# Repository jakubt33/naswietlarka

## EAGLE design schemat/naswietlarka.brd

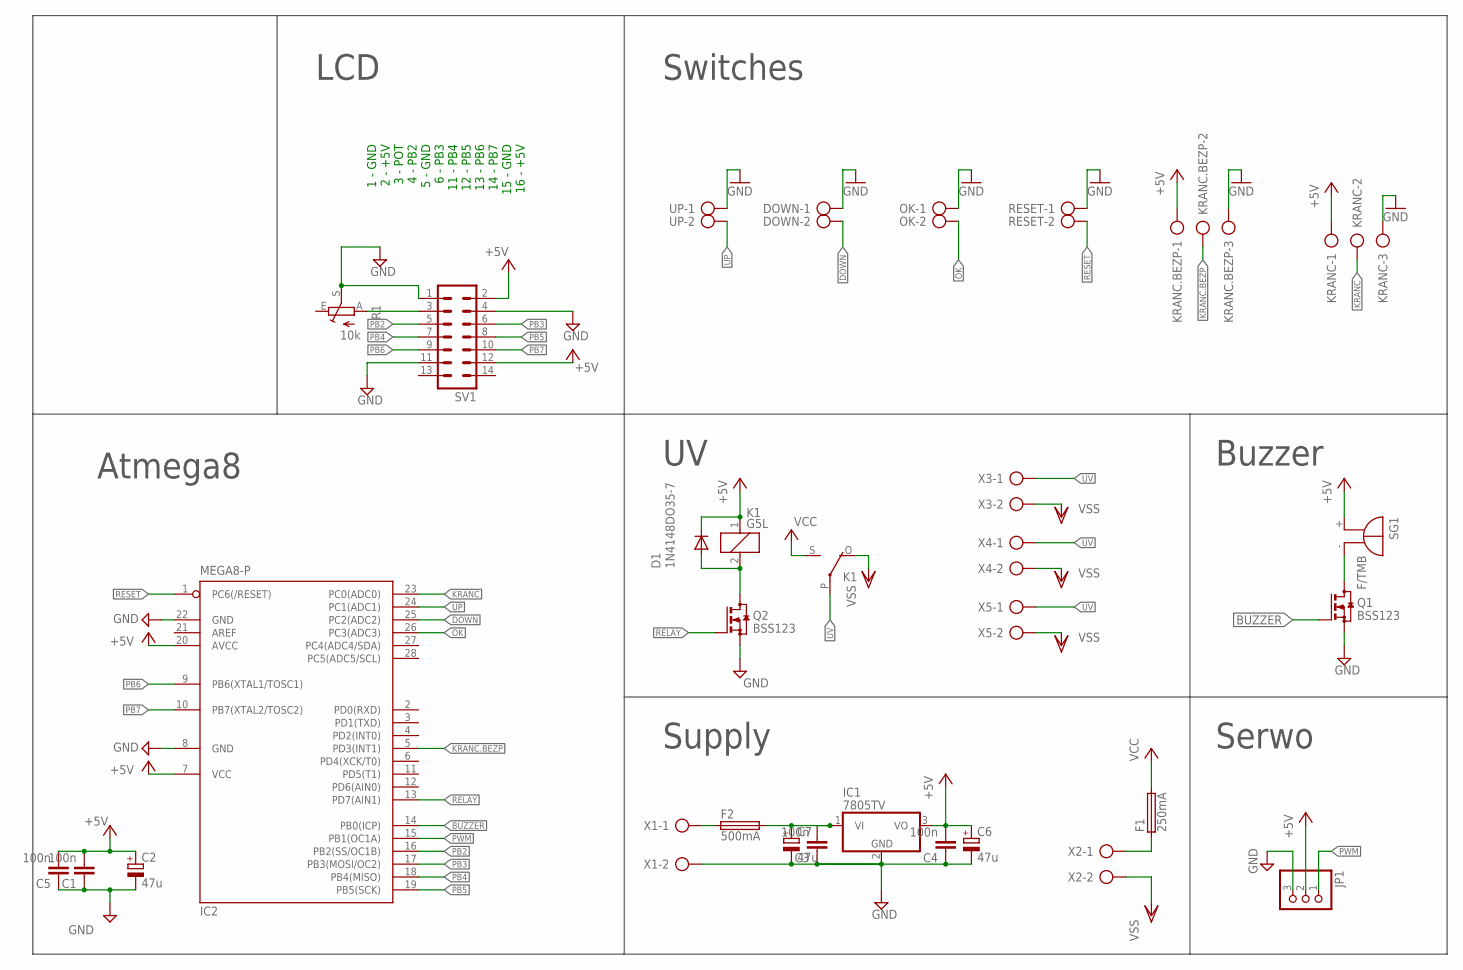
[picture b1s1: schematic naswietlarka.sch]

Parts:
C1, C3, C4, C5: 100n; C0805
C2, C6, C7: 47u; E2,5-5
D1: 1N4148DO35-7; DO35-7
DOWN: AK300/2
F1: 250mA; SH22,5
F2: 500mA; SH22,5
IC1: 7805TV; TO220V
IC2: MEGA8-P; DIL28-3
JP1: PINHD-1X3; 1X03
K1: G5L; G5LE
KRANC, KRANC.BEZP: AK300/3
OK: AK300/2
Q1, Q2: BSS123; SOT23
R1: 10k; CA6V
RESET: AK300/2
SG1: F/TMB
SV1: ML14
UP: AK300/2
X1, X2, X3, X4, X5: AK500/2-H

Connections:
+5V: C1.2, C2.+, C4.2, C5.2, C6.+, D1.C, IC1.3 (VO), IC2.7 (VCC), IC2.20 (AVCC), JP1.2, K1.1, KRANC.1, KRANC.BEZP.1, SG1.+, SV1.2, SV1.12
BUZZER: IC2.14 (PB0(ICP)), Q1.1 (G)
DOWN: DOWN.2, IC2.25 (PC2(ADC2))
GND: C1.1, C2.-, C3.1, C4.1, C5.1, C6.-, C7.-, DOWN.1, IC1.2 (GND), IC2.8 (GND), IC2.22 (GND), JP1.3, KRANC.3, KRANC.BEZP.3, OK.1, Q1.2 (S), Q2.2 (S), R1.S, RESET.1, SV1.1, SV1.4, SV1.11, UP.1, X1.2
KRANC: IC2.23 (PC0(ADC0)), KRANC.2
KRANC.BEZP: IC2.5 (PD3(INT1)), KRANC.BEZP.2
unnamed: R1.A, SV1.3
unnamed: D1.A, K1.2, Q2.3 (D)
unnamed: F1.1, X2.1
unnamed: Q1.3 (D), SG1.-
unnamed: F2.1, X1.1
unnamed: C3.2, C7.+, F2.2, IC1.1 (VI)
OK: IC2.26 (PC3(ADC3)), OK.2
PB2: IC2.16 (PB2(SS/OC1B)), SV1.5
PB3: IC2.17 (PB3(MOSI/OC2)), SV1.6
PB4: IC2.18 (PB4(MISO)), SV1.7
PB5: IC2.19 (PB5(SCK)), SV1.8
PB6: IC2.9 (PB6(XTAL1/TOSC1)), SV1.9
PB7: IC2.10 (PB7(XTAL2/TOSC2)), SV1.10
PWM: IC2.15 (PB1(OC1A)), JP1.1
RELAY: IC2.13 (PD7(AIN1)), Q2.1 (G)
RESET: IC2.1 (PC6(/RESET)), RESET.2
UP: IC2.24 (PC1(ADC1)), UP.2
UV: K1.P, X3.1, X4.1, X5.1
VCC: F1.2, K1.S
VSS: K1.O, X2.2, X3.2, X4.2, X5.2

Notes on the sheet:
LCD
Switches
Atmega8
Supply
Buzzer
Serwo
1 - GND 2 - +5V 3 - POT 4 - PB2 5 - GND 6 - PB3 11 - PB4 12 - PB5 13 - PB6 14 - PB7 15 - GND 16 - +5V

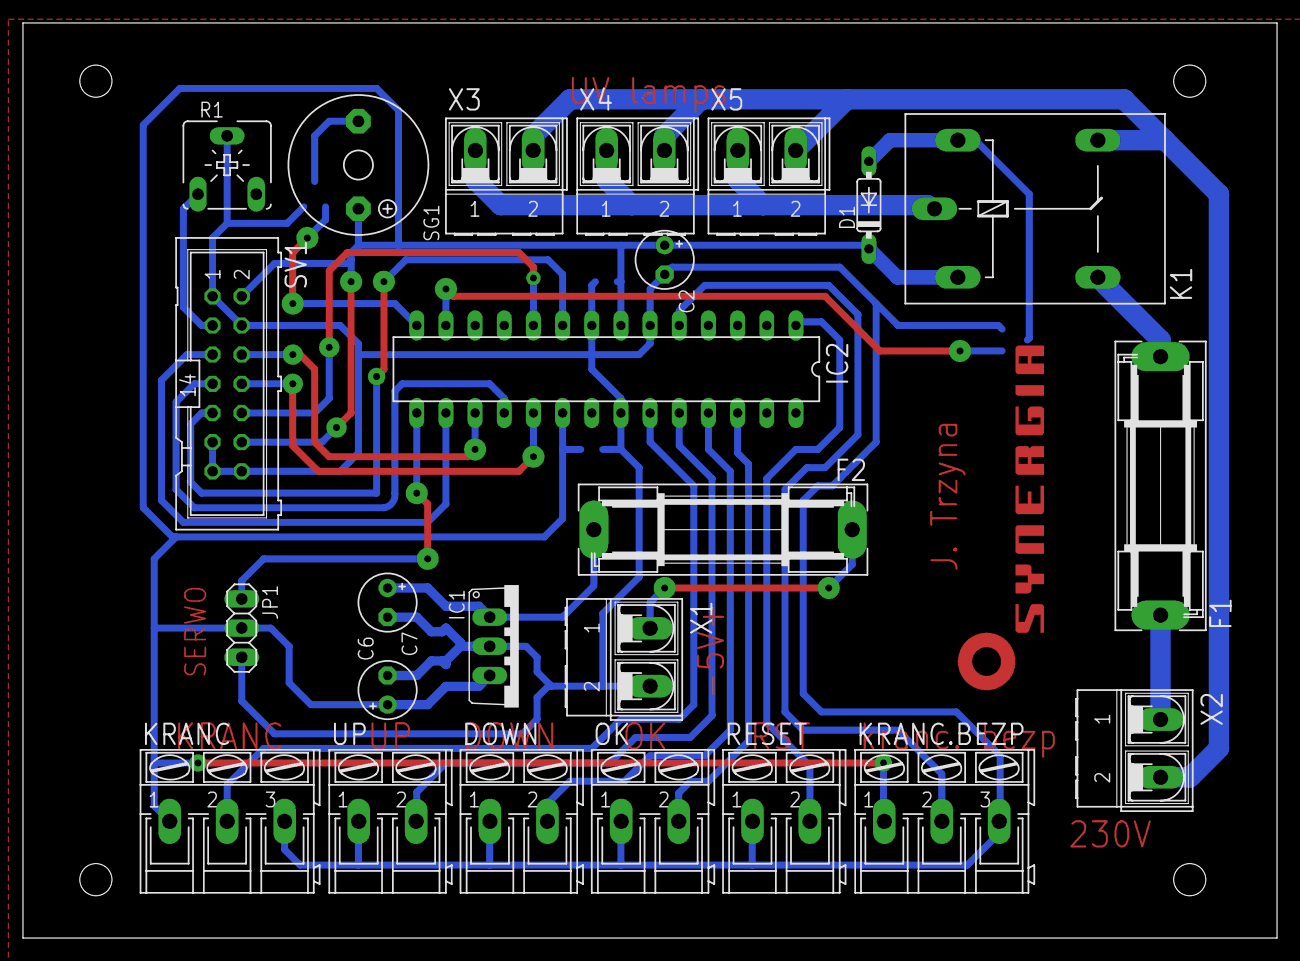
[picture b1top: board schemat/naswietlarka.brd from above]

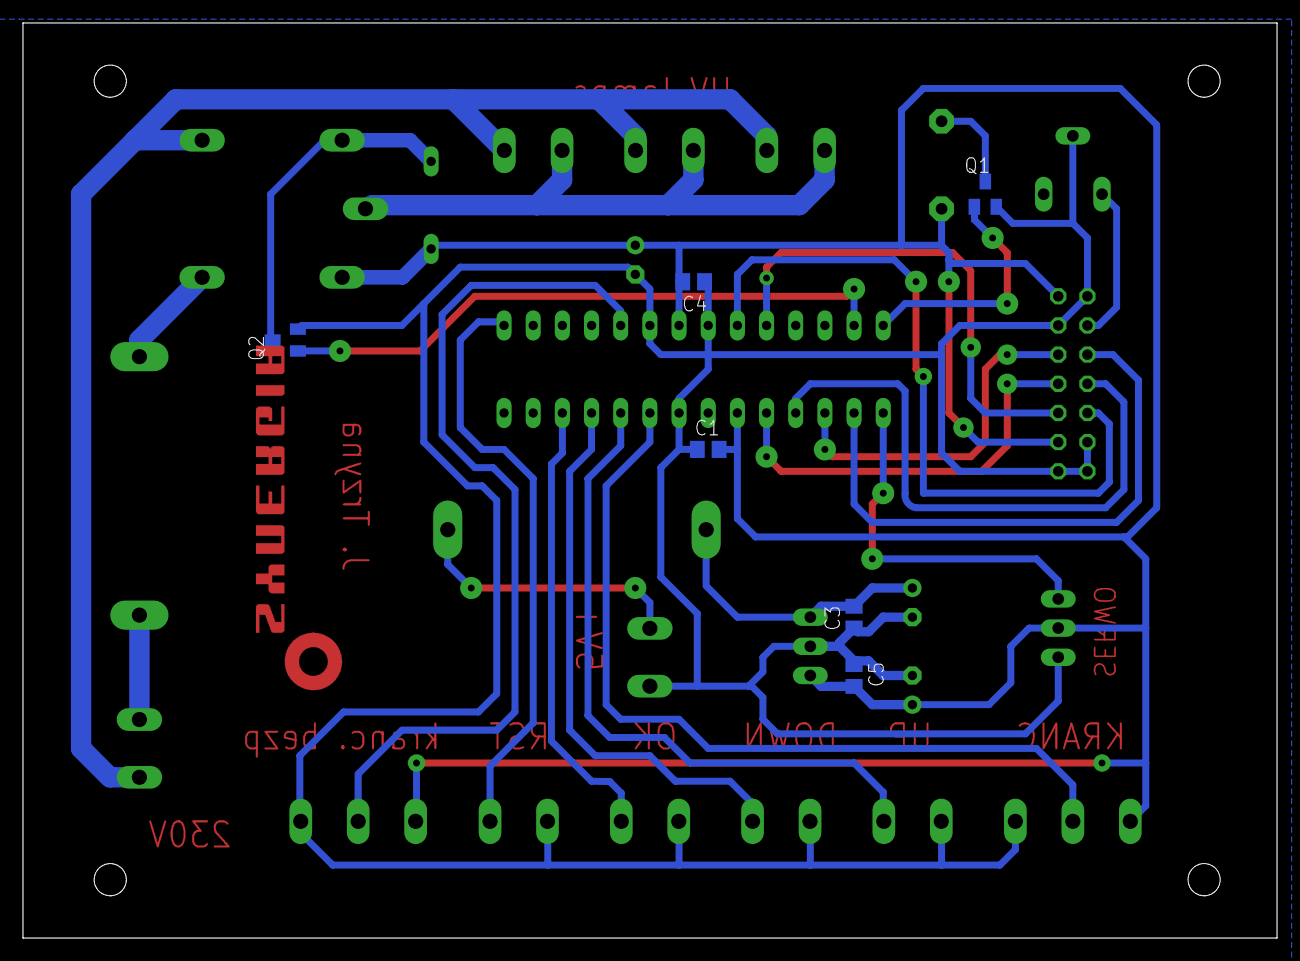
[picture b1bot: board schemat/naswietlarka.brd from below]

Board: 2 copper layers, 109.2 x 79.7 mm, 31 parts (6 on the bottom side), 26 nets.

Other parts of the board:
U$1: SYNERGIA_30MM

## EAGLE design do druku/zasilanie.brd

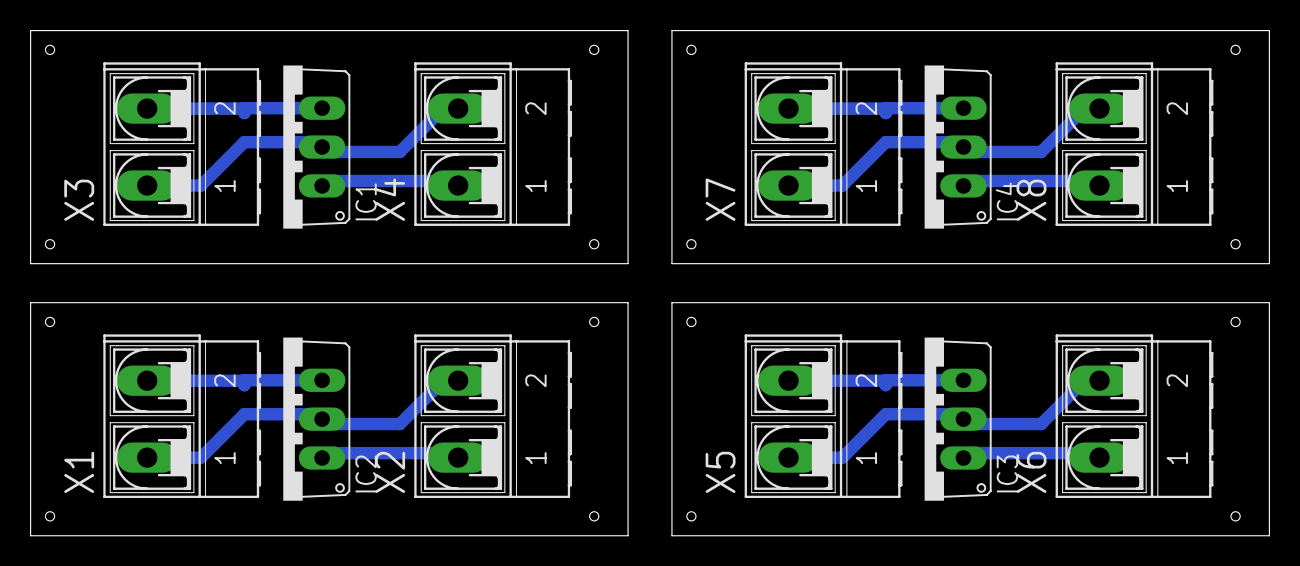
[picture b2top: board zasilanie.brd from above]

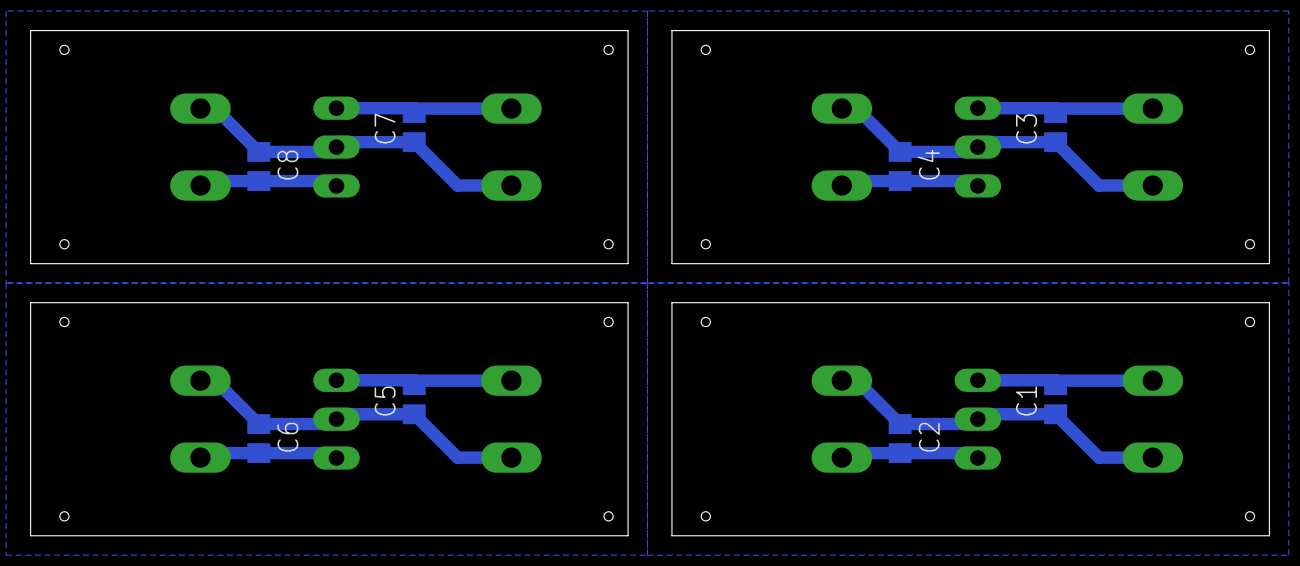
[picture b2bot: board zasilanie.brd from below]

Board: 2 copper layers, 81.0 x 33.0 mm, 20 parts (8 on the bottom side), 12 nets.

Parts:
C1, C2, C3, C4, C5, C6, C7, C8: 100n; C0805
IC1, IC2, IC3, IC4: 7805TV; TO220V
X1, X2, X3, X4, X5, X6, X7, X8: AK500/2-H

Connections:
GND: C1.1, C2.1, IC2.2, X1.1, X2.2
GND1: C3.1, C4.1, IC1.2, X3.1, X4.2
GND2: C5.1, C6.1, IC3.2, X5.1, X6.2
GND3: C7.1, C8.1, IC4.2, X7.1, X8.2
unnamed: C1.2, IC2.3, X1.2
unnamed: C2.2, IC2.1, X2.1
unnamed: C3.2, IC1.3, X3.2
unnamed: C4.2, IC1.1, X4.1
unnamed: C5.2, IC3.3, X5.2
unnamed: C6.2, IC3.1, X6.1
unnamed: C7.2, IC4.3, X7.2
unnamed: C8.2, IC4.1, X8.1

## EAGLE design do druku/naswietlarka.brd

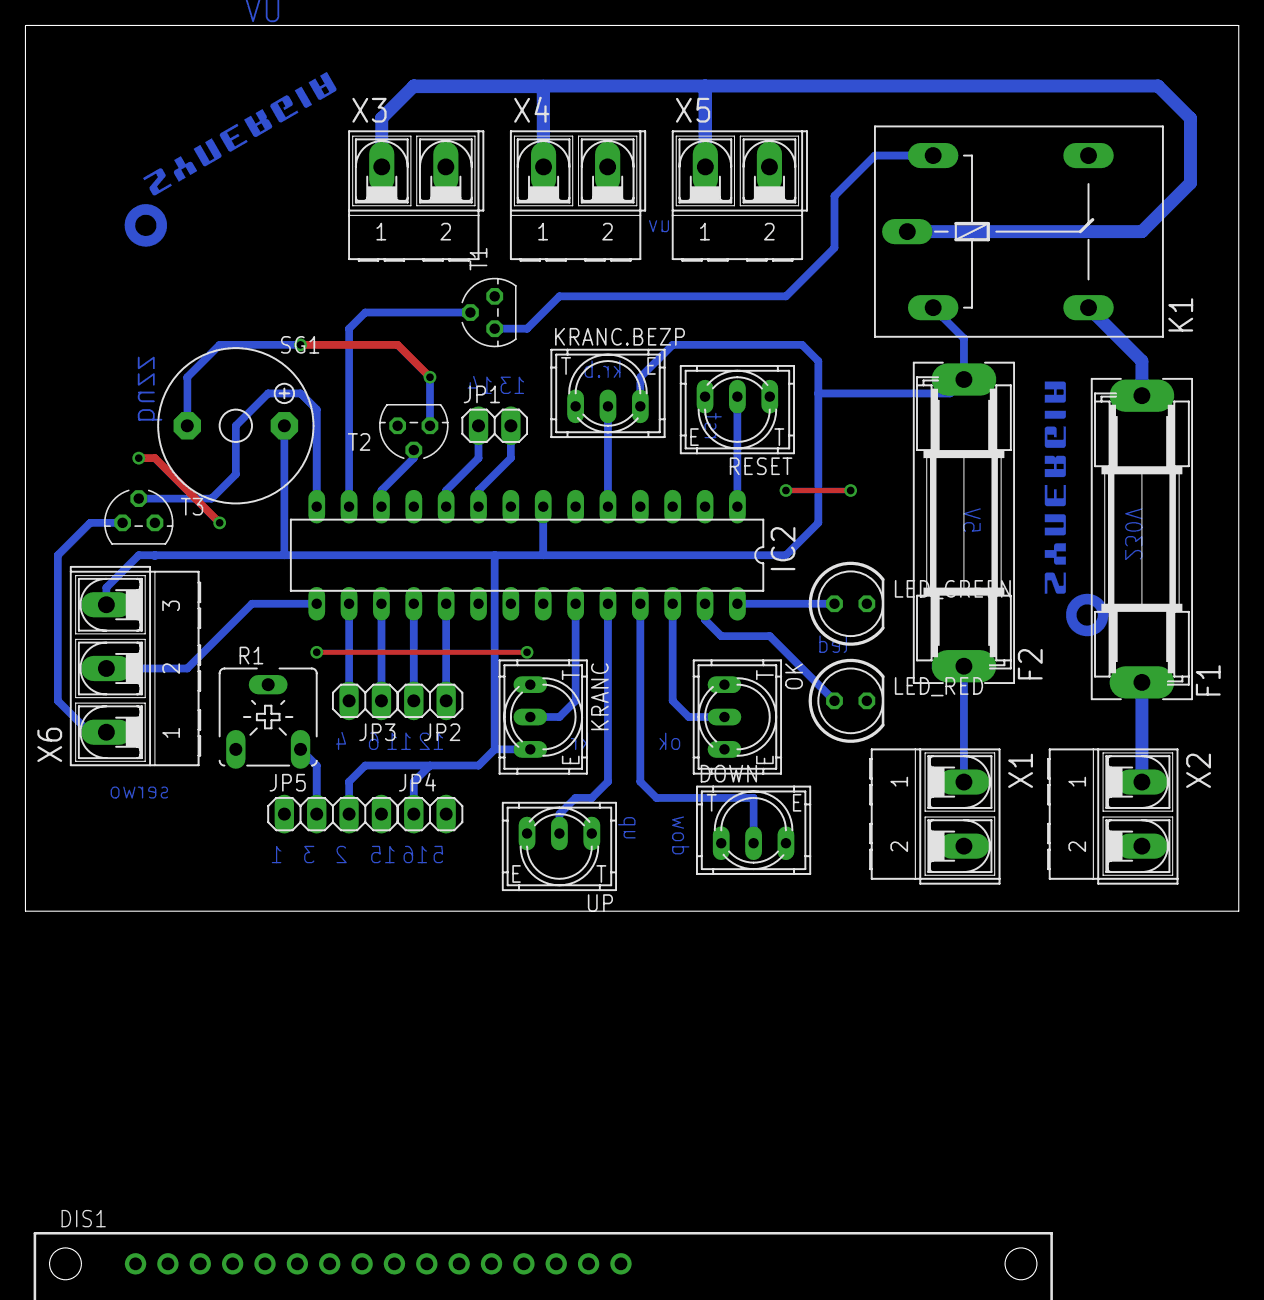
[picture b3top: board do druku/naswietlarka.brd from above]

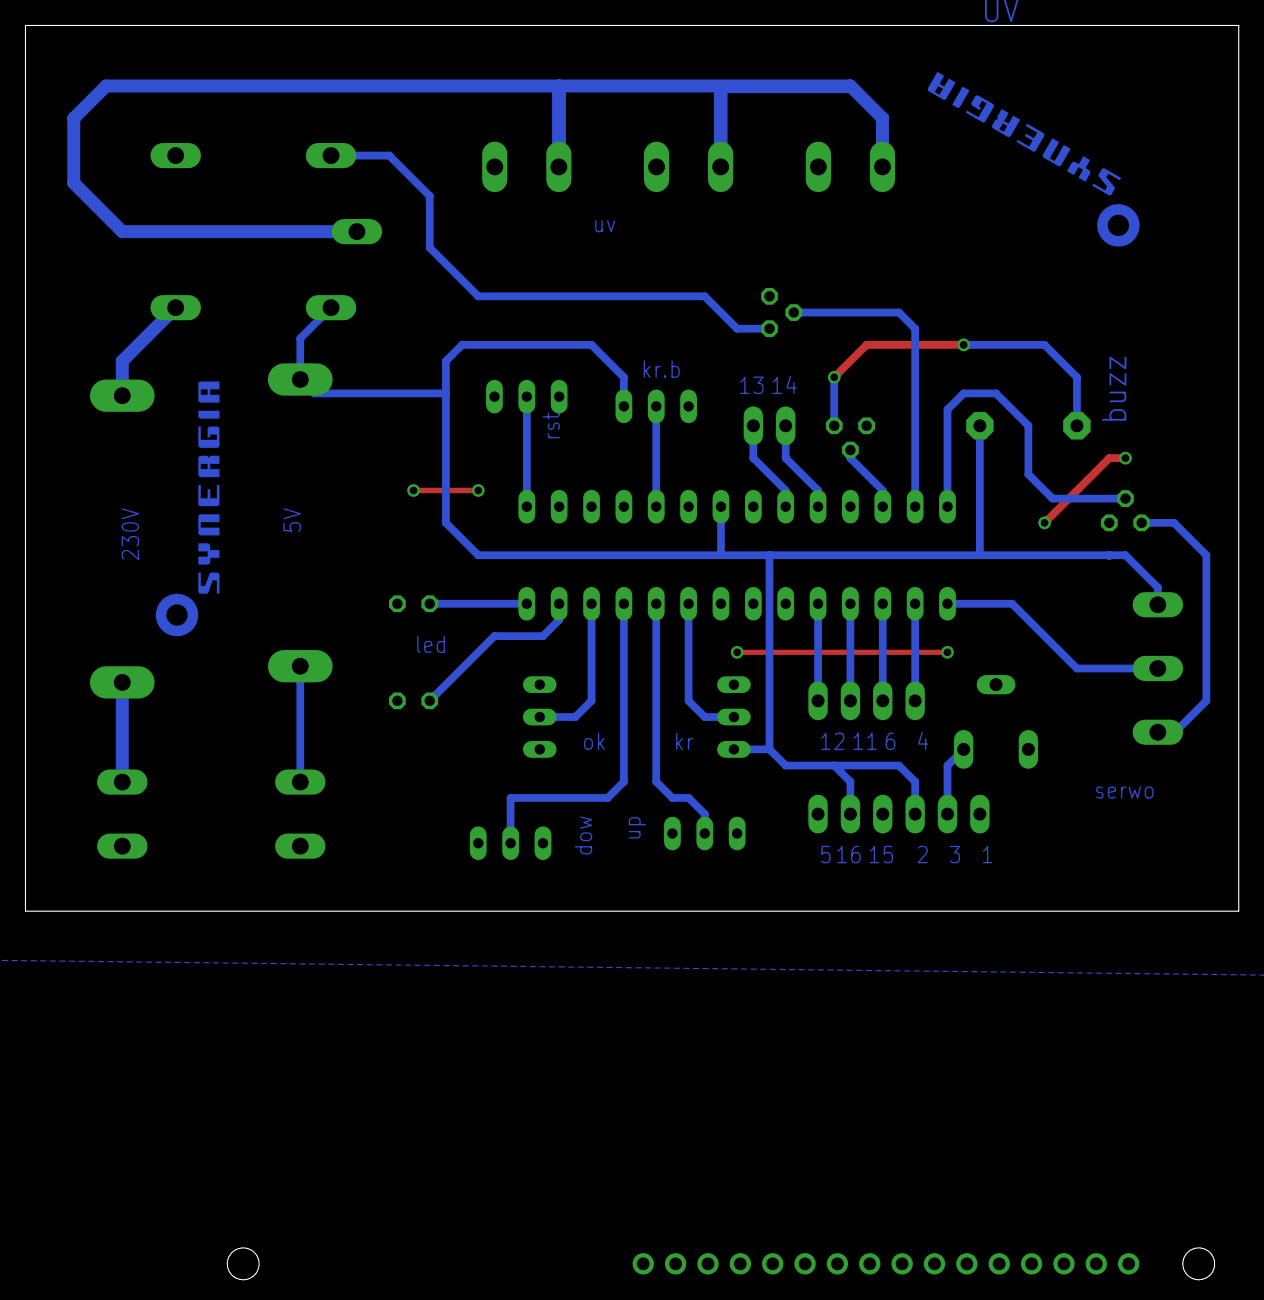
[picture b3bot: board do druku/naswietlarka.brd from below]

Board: 2 copper layers, 95.2 x 69.5 mm, 31 parts (2 on the bottom side), 28 nets.

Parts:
DIS1: TUXGR_16X2_R2
DOWN: 9077-1
F1, F2: SH22,5
IC2: MEGA8-P; DIL28-3
JP1, JP2, JP3, JP4: 1X02
JP5: 1X04
K1: G5L; G5LE
KRANC, KRANC.BEZP: 9077-1
LED_GREEN: LED5MM
LED_RED: LED5MM
OK: 9077-1
R1: CA6V
RESET: 9077-1
SG1: F/TMB
T1, T2, T3: BC547; TO92
U$1, U$2: SYNERGIA_20MM
UP: 9077-1
X1, X2, X3, X4, X5: AK500/2-H
X6: AK500/3-H

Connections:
+5V: F2.2, IC2.7, JP4.1, JP5.3, K1.1, KRANC.3, KRANC.BEZP.3, SG1.+, X6.3
BUZZER: IC2.12, T2.2
DOWN: DOWN.2, IC2.25
EN_PWM: IC2.14, T3.2
GND: DOWN.1, IC2.8, IC2.22, JP4.2, JP5.1, JP5.4, K1.O, KRANC.1, KRANC.BEZP.1, LED_GREEN.K, LED_RED.K, OK.1, R1.S, RESET.1, T1.1, T2.1, T3.1, UP.1, X1.2, X2.2, X3.2, X4.2, X5.2
KRANC: IC2.23, KRANC.2
KRANC.BEZP: IC2.5, KRANC.BEZP.2
LED_GREEN: IC2.28, LED_GREEN.A
LED_RED: IC2.27, LED_RED.A
unnamed: JP5.2, R1.E
unnamed: K1.2, T1.3
unnamed: F1.1, X2.1
unnamed: SG1.-, T2.3
unnamed: F2.1, X1.1
unnamed: T3.3, X6.1
OK: IC2.26, OK.2
PB2: IC2.16, JP3.2
PB3: IC2.17, JP3.1
PB4: IC2.18, JP2.2
PB5: IC2.19, JP2.1
PB6: IC2.9, JP1.2
PB7: IC2.10, JP1.1
PWM: IC2.15, X6.2
RELAY: IC2.13, T1.2
RESET: IC2.1, RESET.2
UP: IC2.24, UP.2
UV: K1.P, X3.1, X4.1, X5.1
VCC: F1.2, K1.S

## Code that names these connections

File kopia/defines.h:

#ifndef DEFINES_H_INCLUDED
#define DEFINES_H_INCLUDED


#define F_CPU 4000000UL
#define __DELAY_BACKWARD_COMPATIBLE__

#include <avr/io.h>
#include <util/delay.h>
#include <avr/interrupt.h>
#include <string.h>

int flag_kierunek = 0;

//MAIN
#define NIE 0
#define TAK 1

#define PRZOD 1
#define TYL -1
#define STOP 0
#define MIN_DLUGOSC 6

int ilosc_petli();
int get_distance();
void wykonaj (int, int);
void beep();
void pozycjonowanie();
//

//INIT
#define DDR_BUZZER DDRD
#define PORT_BUZZER PORTD
#define BUZZER PD6

#define RELAY PD7
#define PORT_RELAY PORTD
#define DDR_RELAY DDRD

void init_LCD();
void init_PWM();
void init_Switch();

void init_Buzzer();
void buzzer_off();
void buzzer_on();

void init_ralay();
void relay_on();
void relay_off();
//

//PWM
#define PWM 1
#define EN_PWM 0
#define MIN_PWM 20
#define MAX_PWM 255

void kierunek(int gdzie);
void go();
void stop();
//

//SWITCHES
#define PIN_SWITCH PINC
#define KRANC PC0
#define SWITCH_UP PC1
#define SWITCH_DOWN PC2
#define SWITCH_OK PC3
#define DDR_SWITCH DDRC
#define PORT_SWITCH PORTC
//

//LCD
#define DDR_LCD DDRB
#define PORT_LCD PORTB
#define RS_LCD 2
#define EN_LCD 3
#define DB4_LCD 4
#define DB5_LCD 5
#define DB6_LCD 6
#define DB7_LCD 7

void czysc_LCD();
void gen_char(char *ch, int *i);
void push_LCD( int8_t bajt ) ;
void wyswietl_LCD( char *napis);
//


#endif // DEFINES_H_INCLUDED

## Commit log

2014-02-05 demo LCD+PWM
2014-02-06 problem z przyciskami, silnik tylko przyspiesza
2014-02-06 menu w wersji alfa, przyciski + pwm
2014-02-06 ustawianie ilosci petli
2014-02-07 wyswietlanie liczb-ilosci petli
2014-02-07 polepszenie przejrzystosci kodu
2014-02-28 pozycjonowanie i jazda od krancówki do krancowki
2014-03-14 jazda 1.5s do przodu i powrot, ilosc petli konfigurowalna
2014-03-14 włącznie buzzera i relaya
2014-03-17 wszystkie funkcje dzialają, brak regulacji odleglosci i defaultowych wartosci
2014-03-20 wybor dlugosci plytki
2014-03-21 ustawianie czasu a nie ilosci petli
2014-03-27 poprawne odlicznie, wartosci defaultowe
2014-04-16 porawa wyswietlacza
2014-11-09 poprawiona wersja schematu i płytki
